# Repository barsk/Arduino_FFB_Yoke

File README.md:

# SimInvent FFB Yoke 
A Force Feedback Yoke based on 775 DC motors and an Arduino (SparkFun) Micro Pro microcontroller. 

This is a fork of [Gagagu Arduino FFB Yoke](https://github.com/gagagu/Arduino_FFB_Yoke). The goals of this fork was to lower total cost, add new features, achieve a smaller footprint, use cheaper and use more accurate AS5600 magnetic encoders and maximize pitch travel distance.

# Documentation
***All build guides and documentation for the 3D printed parts, electronics and software are in the [Wiki section!](https://github.com/barsk/Arduino_FFB_Yoke/wiki/Home)***

# Support
The [SimInvent Discord Server](https://discord.gg/cZUywYGyt6) is the main support and chat channel for this project. You are welcome to chime in and join the community there!<br>
**Bug reports**, please create an [Issue](https://github.com/barsk/Arduino_FFB_Yoke/issues) so we can track bugs and issues. 

---

> # Version 1.0 Release
> First public feature complete release with a **host of new features and performance**
>
> ## Firmware
> The firmware is now **highly optimized** compared to the previous version.
> It is now **100% compliant** with the standard Microsoft USB PID 1.0 specification with the following notable changes and bug fixes:
> * Force loop rate runs about  **2.5 times as fast** due to optimizations in every part of the firmware - 
> * Sine lookup table with interpolation replaces the computationally expensive sin() function in the force loop  - Contributing 45% of the speedup in the force loop
> * Effect direction now follows the DirectInput specification fully - Force directions was previously **inversed** in some situations
>* Multi-second FFB command lag removed when several effects were playing simultaneously with high framerate - 
> Due to inefficient USB protocol reads the input queue could build up and cause multi second lag
> * Effects no longer cancel or distort each other under load - The force calculator routine summed up effect forces 
> incorrectly causing an internal integer overflow
> * Coasting at idle - The motor output stage was driven even when idle, so the yoke was efffectively braked when zero force was applied. This has now been fixed, at 0 force, the output stage disbles leaving the yoke unpowered.
> * Handling non-linear motor response - The 775 motor driven straight from a PWM from 0-255 will yield a non-linear response. First at PWM=~25-40 the axis will start to move at all. Not handled this will create a huge deadband. We have previously handled this in the Setting tool with a "Motor Start Power" to define a starting point from which the effects should start, that settles the starting point, but the response *over* that setting will be non-linear with an initial bump unrealistically amplifying small effect forces. There are now settings in the firmware to configure the handling of this. See [Handling non-linear motor response](https://github.com/barsk/Arduino_FFB_Yoke/wiki/Firmware#handling-non-linear-motor-response) in the Wiki Firmware section.
>
> ## New pitch axis design
> 
> The pitch axis previously featured a planetary gear on the motor. That gave the axis plenty of torque, but also introduced backlash 
> and friction. The backlash creates a lot of rattle on vibration effects and the friction makes the axis a bit numb on smaller forces.
> The new design removes the planetary gear and instead uses a 14T pulley with a 720 mm belt. This trades some of torque, but the pitch axis is still about 70% stronger than roll anyway. 
> The upside is that **pitch now feels nimble and direct**, you are more connected to the sim and aircraft and can feel it in you hands.  
> 
> If you built the former 30T + gears based version you need to get a new metal motor bracket (same as on roll), a 14t pulley and a 720 mm belt. You will also need to print a new idler pulley (also 14T), print a new frame belt clamp piece for the new raised belt position, and a new pitch motor mount for the new height.
>
> The previous design with planetary gears can still be used, see Wiki for details.
> ## FFBTestTool

>There is now a new bundled **FFBTestTool.exe**, replacing the old ForceTest.exe that show you exactly what the 
> firmware sees from your built yoke, helping diagnosing magnetic encoders, travel, reversed motor wiring and 
> other faults, and confirming that every FFB effect is running and performing as expected with a graphical 
> view of the yoke and the forces applied to it.\
> Full details in https://github.com/barsk/FFBTestTool
> 
> ## Electronics
> The new PCBs (circuit boards) are now **fully tested!** Many thanks to **@PeteDDD** for his valuable contribution. All details are in the Wiki, Parts List and in the Electronics folder.

# Design and features compared to Gagagu Yoke

* Completely new CAD design with focus on easy printing and assembly.
* New PCB design.
* Magnetic AS5600 encoders featuring 12 bit accuracy, saving cost, space and weight.
* Removed planetary gears in both roll and pitch axis which introduces backlash (slop), friction and considerable weight increasing mass and inertia. Roll axis with a 56T pulley, 12T motor drive. That gives a 4.7 gear ratio which is quite enough for roll forces and provides a more nimble, lively feel than the old design. Pitch axis now uses a 14T pulley. 
* Reduced footprint (400 x 275 x 100 mm).
* Pitch travel up to 165 mm with 720 mm belt on pitch (Y) axis. 
* Configurable pitch travel range in the settings tool.
* Default centering Spring force when non-FFB games are played.
* Yoke controller is remixed so that only 3 mm brass thread inserts is used. The mount bracket is updated for strength.
* Calibration method is completely revamped. It runs automatically on first start to find the endstops (IR sensors) at the extremes of the axis travel. It can also be manually started by a button at any time. 
* The calibration data is stored in EEPROM and recalled on subsequent reboot. 
* Cable chain link. To prevent breakage of the cabling a chain link is used in the design. This will give all cables from the yoke handle and frame sensors a controlled bend characteristic with a big radius preventing acute bending and breakage. 
* A 3D printed casing with plenty of cooling slots for ventilation is part of the design and fully integrated. The casing is split up into four parts plus the front and back panels which is split in two each, providing a fully printable design despite its large size. The parts are assembled with (printed) dowels and glued or screwed together.

### Electronics and PCB (circuit boards)
**@PeteDDD** has graciously contributed new custom PCB designs. 
Gagagu version PCBs can still be used, with some modifications (see Wiki).

### Settings tool
A settings tool written in Python and Qt6. The tool features a sleek experience and features a robust and fast serial protocol.

### 3D printed parts
No 3D printed parts are the same from the Gagagu/jwryan4 project. Every part has been redesigned from the ground up with focus on easy printing, strength, functionality and minimal footprint. The IR-based end-stop sensors are now integrated into the actual design in a way that need no careful positioning as before.

### Firmware
The firmware code is *heavily modified and enhanced* with new features and updated for the new AS5600 encoders and a TCA9548 I2C mux. 
With heavy optimizations it was possible to squeeze all the performance and features into the Atmega32u4 28 KB Flash ROM of the Arduino Pro Micro with just a few bytes to spare!

### FFB Effects
The actual FFB effects are based on the [FINO](https://github.com/jmriego/Fino) project but have undergone bug fixes and heavy optimization to increase speed, lower latency and lower FLASH size.

#### Games with native FFB
For games that themselves handles standard FFB effects such as IL2 and DCS the yoke will work when connected, as it fully handles the standard DirectInput PID protocol (currently untested, but *should* work!).

 ####  Microsoft Flight Simulator, Xplane and others without FFB effects
 Since MSFS and others don't have any FFB effects implemented we have to rely on external software to interpret telemetry data from the sim and create effects accordingly. 

 * [**DirectLink** with **TelemFFB** from VPForce](https://directlink.flyfrisby.com/) A new contender, **free** download, which creates the link between TelemFFB, which formerly only could only interact with its own Rhino devices, can now interact with standard DirectInput FFB devices. Currently in Beta, but works fine with SimInvent FFB Yoke! 
 
* [FFB-Bridge](https://ffb-bridge.com/) - A great **free** force-feedback application for flight simulators on Windows, Linux, and macOS, developed and published by Rohsam Inc.

 * [XPForce](https://www.fsmissioneditor.com/product/xpforce/) - Commercial product (subscription), works for MSFS, Xplane, Flight Sim world and Prepar3D. 
 
I am not affiliated with these softwares, nor is this in any way a comprehensive list, there may be other options.

### Assembly
For easy assembly there is a number of options: 

* A printable "bracket" that can be used to position the right rail correctly. The other parts will then be easy to postition relatively that rail or the edge of the board. 
* Drill template (drawing) for the bottom board that can be printed in 1:1 scale and layed out on the board to easily position the components. 
* The STEP file of the board with all (threaded) screw holes in the correct spots can be used to machine the board on a CNC router. 

These method are described in the [Wiki Build-Guide](https://github.com/barsk/Arduino_FFB_Yoke/wiki/Build-Guide).

## Limitations
The design has some drawbacks that need to be taken in consideration.

* DC motors are not as efficent as brushless BLDC motors. They overheat sooner if pushed hard.  
* There is a slight cogging sensation in the rotation of these motors than with BLDC motors (that can use anti-cogging algorithms in the motor drivers to counter the effect)
* The microprocessor is limited to 16 MHz which leaves little headroom if many effects are playing simultaneously. There heas been a great effort put into finding optimizations on every possible front to squeeze the absolute most of this device. With about 10-15 effects playing at the same time we can do periodics (sine, triangle etc) up to about 90-100 Hz, which should cover most if not all real world scenarios. And if we reach the ceiling the periodic will drop a little in frequency, that is basically all.

The motors (775 DC) and BTS7960 43A drivers are easy to find and come at a very low cost. Better microprocessors, BLDC motors and drivers are at the next level cost wise, and what we achieve with these components is pretty impressive!
Just keep in mind the possible overheating problems and do not use strong forces sustained for a prolonged time as this can overheat the motors. Heatsinks on the motors and a fan controller that kicks in at about 40 centigrades is mandatory. When you hear the fan power up, you know you are pushing it. That said, when flying normally with the aircraft properly trimmed this practically never occurs. Heatsinks, fan controllers and fans are all in the Parts List (see [Wiki section](https://github.com/barsk/Arduino_FFB_Yoke/wiki/Part-List)).

## Credits
*I wish to thank **@PeteDDD** for invaluable help with professional level proof reading and for the new quality PCBs.*

### Some of the Github projects this is based on.
* [FINO](https://github.com/jmriego/Fino)
* [Rob Tillaart, AS5600](https://github.com/RobTillaart/Arduino/tree/master/libraries/AS5600)
* [Rob Tillaart, TCA9548](https://github.com/RobTillaart/Arduino/tree/master/libraries/TCA9548)

### Thingiverse
* [Cadet Yoke v2.0](https://www.thingiverse.com/thing:4884092)
* [Ender 3 Cable Chain](https://www.thingiverse.com/thing:2920060)

## Using this project commercially is strictly disallowed
If you want to use this project commercially please contact me.

# Disclaimer!
> [!Important]
> Use at your own risk. I am not responsible for any damage or injury to man or machine. Be careful when handling electric installations, electronics and mechanics. If handling electrical installation (230V) by yourself is not legal in your country or you feel unsure of your competence, take proffessional help! <br>
The motors are quite strong and can cause serious injuries if not handled with great caution. The yoke handle can move very quickly when power is applied. Be aware of moving parts, belts and pulleys.

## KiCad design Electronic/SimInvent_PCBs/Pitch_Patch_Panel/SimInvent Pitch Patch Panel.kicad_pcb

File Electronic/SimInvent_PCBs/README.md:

This folder contain the KiCad project files and Gerber files needed for manufacturing of the SimInvent PCBs.

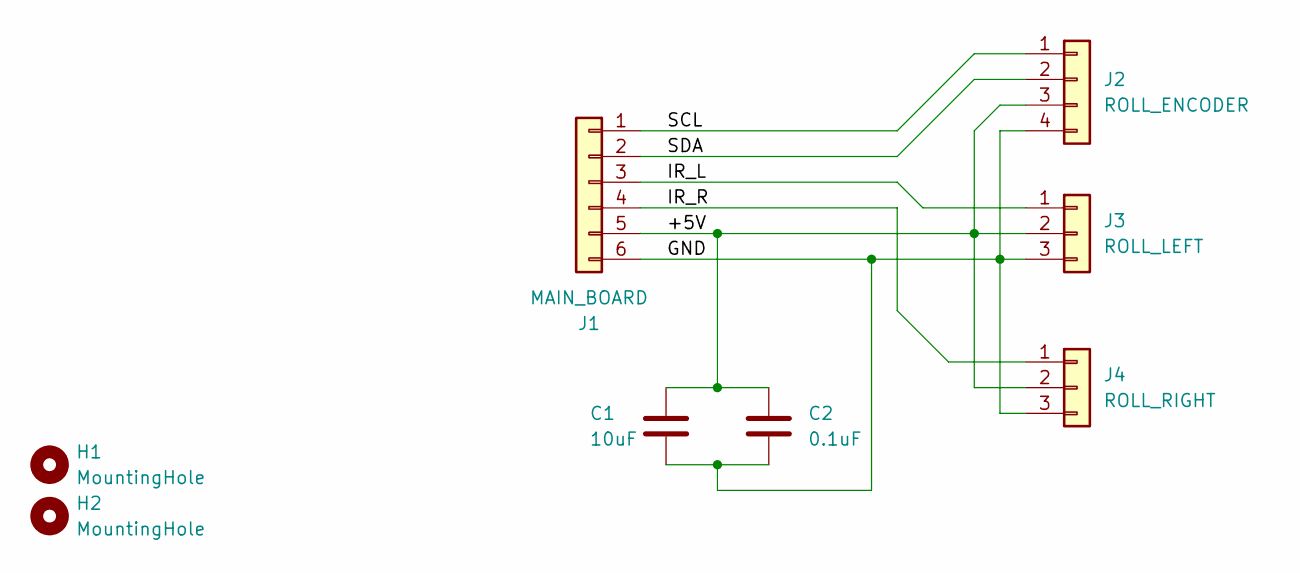
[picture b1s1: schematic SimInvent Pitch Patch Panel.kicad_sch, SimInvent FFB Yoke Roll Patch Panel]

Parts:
C1: 10uF; DUAL_CAP_2.5mm_0603
C2: 0.1uF; DUAL_CAP_2.5mm_0603
H1, H2: MountingHole; MountingHole_3.2mm_M3_DIN965
J1: MAIN_BOARD; JST_XH_B6B-XH-A_1x06_P2.50mm_Vertical
J2: ROLL_ENCODER; JST_XH_B4B-XH-A_1x04_P2.50mm_Vertical
J3: ROLL_LEFT; JST_XH_B3B-XH-A_1x03_P2.50mm_Vertical
J4: ROLL_RIGHT; JST_XH_B3B-XH-A_1x03_P2.50mm_Vertical

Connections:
/+5V: C1.1, C2.1, J1.5, J2.3, J3.2, J4.2
/GND: C1.2, C2.2, J1.6, J2.4, J3.3, J4.3
/IR_L: J1.3, J3.1
/IR_R: J1.4, J4.1
/SCL: J1.1, J2.1
/SDA: J1.2, J2.2

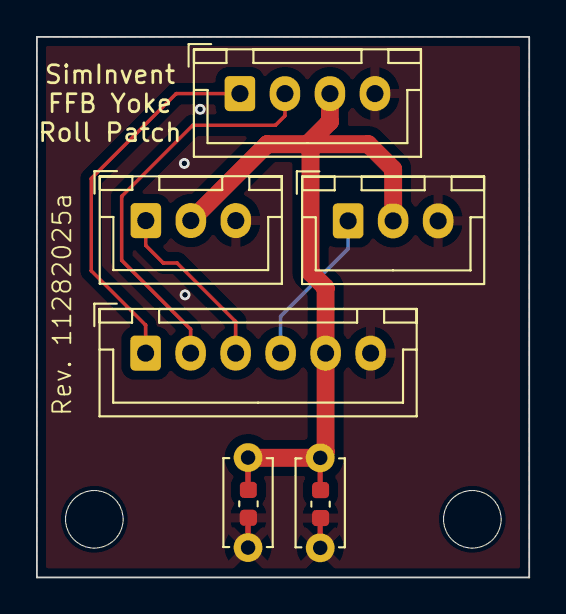
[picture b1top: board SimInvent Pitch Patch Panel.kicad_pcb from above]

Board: 2 copper layers, 27.4 x 30.0 mm, 8 parts (0 on the bottom side), 6 nets.

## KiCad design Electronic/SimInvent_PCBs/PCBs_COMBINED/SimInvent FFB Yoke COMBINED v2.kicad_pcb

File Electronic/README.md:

Contents of this folder:
* Fritzing - source files for the wiring schematics
* SimInvent_PCBs - The new PCBs by @PeteDD
* Legacy - The older Gagagu v2.0 PCBs. These are compatible, but please see the Wiki for details covering the special fixes made.
* PCB_pictures - Rendered PCB images. Note, additional images can also be viewed in the [Wiki Electronics section](https://github.com/barsk/Arduino_FFB_Yoke/wiki/Electronics)
* Wiring_diagram -  Diagram of the overall wiring

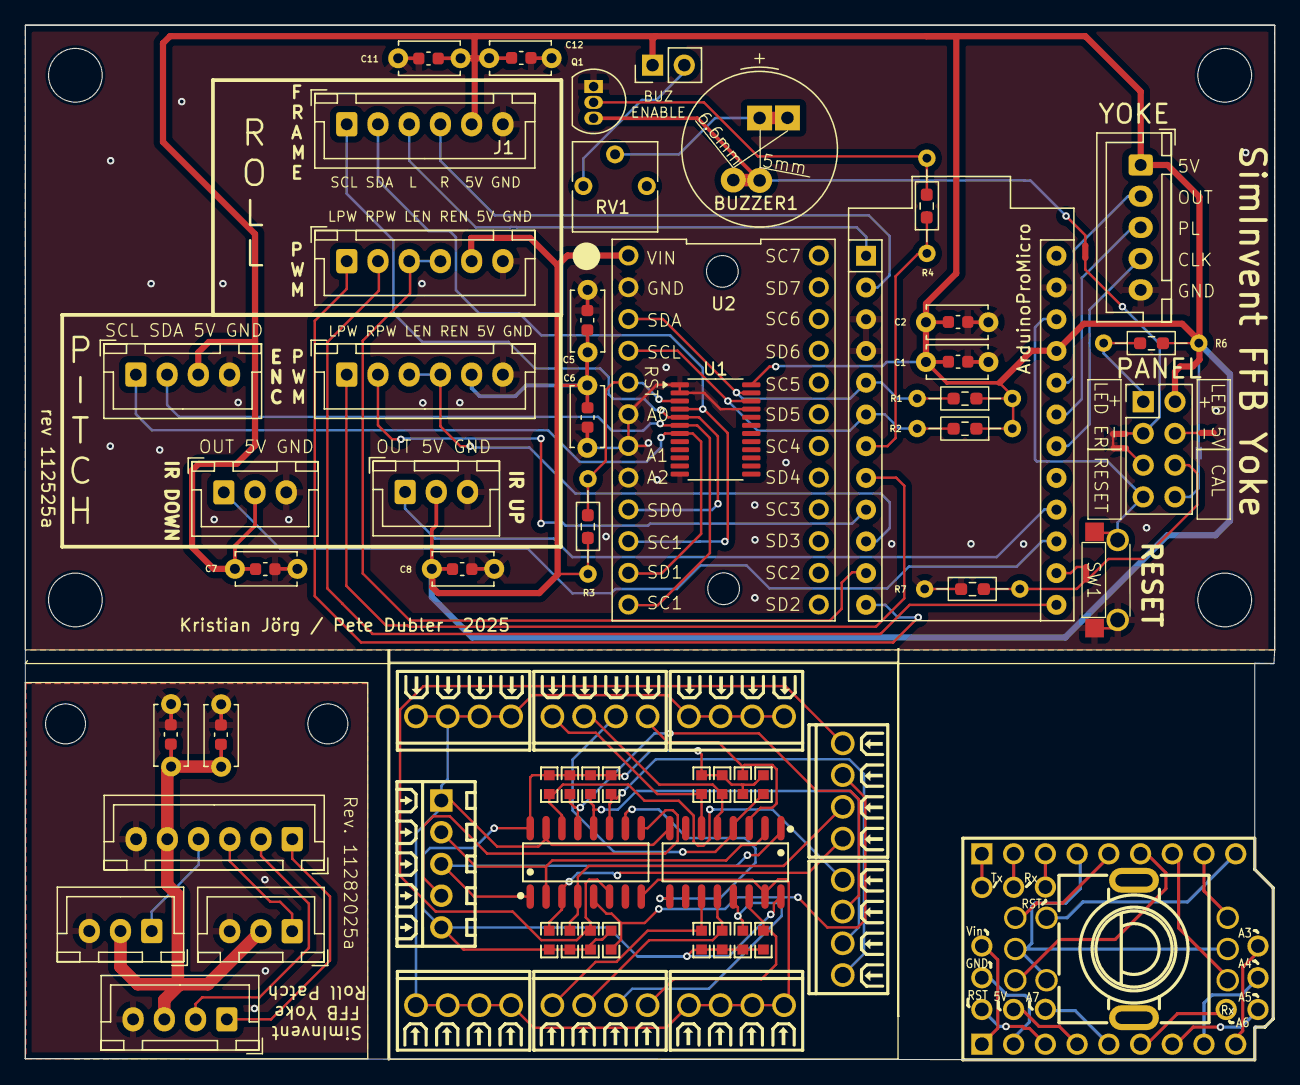
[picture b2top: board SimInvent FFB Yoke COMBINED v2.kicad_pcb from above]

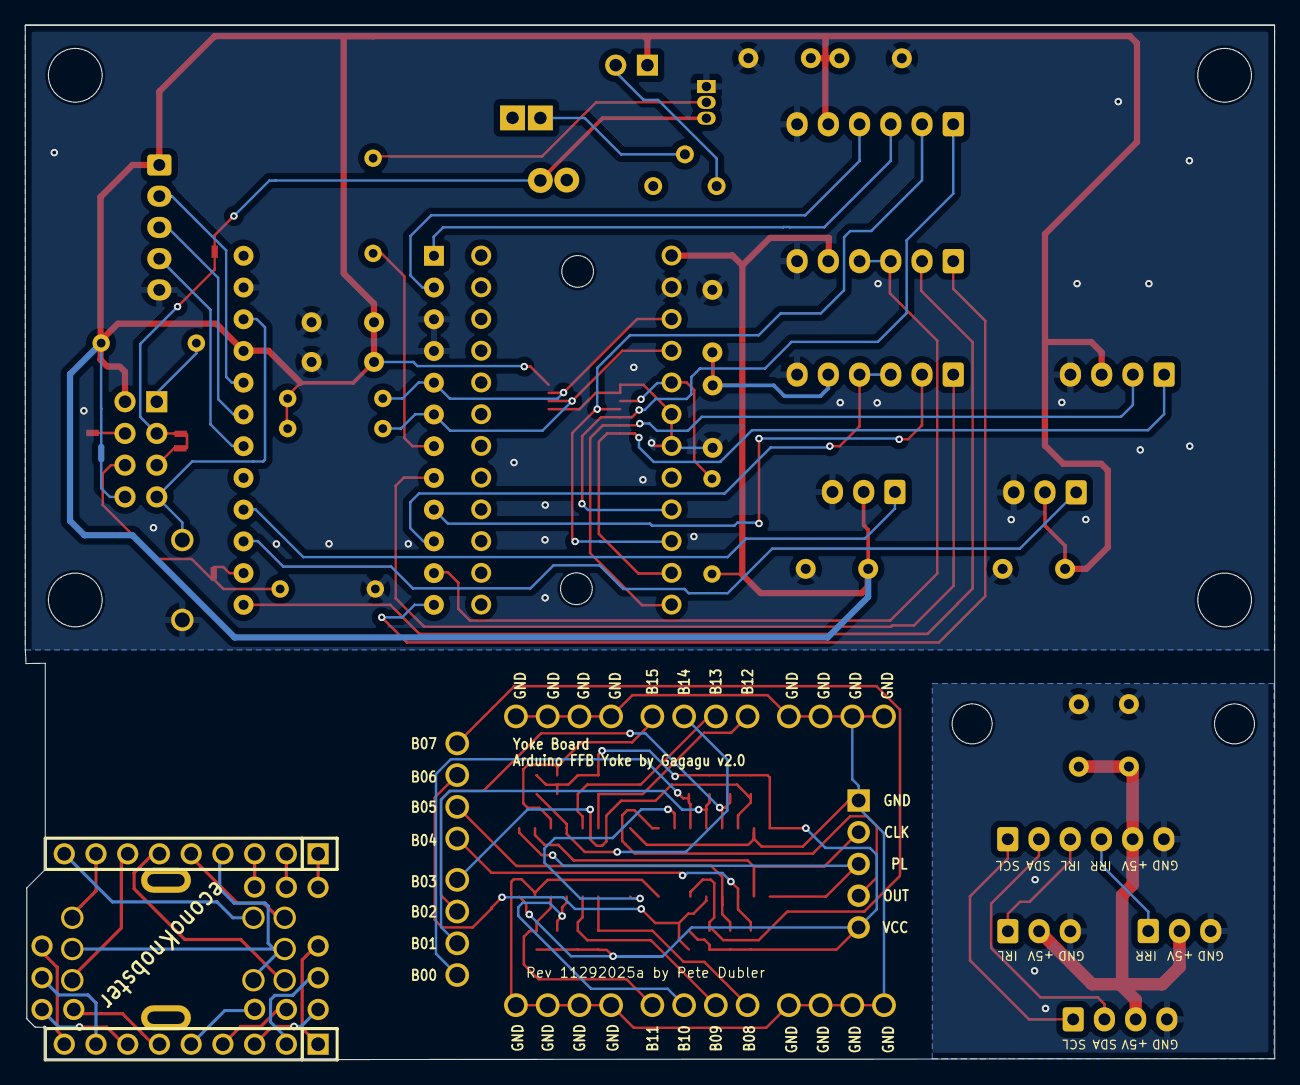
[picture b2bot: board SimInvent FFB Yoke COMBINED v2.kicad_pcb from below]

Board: 2 copper layers, 100.0 x 82.8 mm, 91 parts (2 on the bottom side), 80 nets.

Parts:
ARDUINO_PRO_MICRO1: ArduinoProMicro; Sparkfun_Pro_Micro
BUZZER1: 2700Hz; Buzzer_TDK_PS1240P02BT_D12.2mm_H6.5mm
C1, C2#2, C6, C12: 10uF; DUAL_CAP_2.5mm_0603
C1#2, C2, C5, C7, C8, C11: 0.1uF; DUAL_CAP_2.5mm_0603
H1, H2#2: MountingHole; MountingHole_3.2mm_M3_DIN965
H1#2, H2, H3, H4: MountingHole; MountingHole_4.3mm_M4_DIN965
H1#3, H2#3: HDR-TH_9P-P2.54-V-F-1
H3#2, H4#2, H5, H6, H7, H8, H9, H10, H11, H12, H13, H14: HDR-TH_1P-P2.54-V-M
IC1, IC2: SOIC-16_L9.9-W3.9-P1.27-LS6.0-BL
J1: Frame Cable; JST_XH_B6B-XH-A_1x06_P2.50mm_Vertical
J1#2: MAIN_BOARD; JST_XH_B6B-XH-A_1x06_P2.50mm_Vertical
J2: Roll Motor; JST_XH_B6B-XH-A_1x06_P2.50mm_Vertical
J2#2: ROLL_ENCODER; JST_XH_B4B-XH-A_1x04_P2.50mm_Vertical
J3: Pitch Motor; JST_XH_B6B-XH-A_1x06_P2.50mm_Vertical
J3#2: ROLL_LEFT; JST_XH_B3B-XH-A_1x03_P2.50mm_Vertical
J4: Pitch Encoder; JST_XH_B4B-XH-A_1x04_P2.50mm_Vertical
J4#2: ROLL_RIGHT; JST_XH_B3B-XH-A_1x03_P2.50mm_Vertical
J5: IR Pitch Down; JST_XH_B3B-XH-A_1x03_P2.50mm_Vertical
J6: IR Pitch Up; JST_XH_B3B-XH-A_1x03_P2.50mm_Vertical
J7: Jumper - Buzzer Active; PinHeader_1x02_P2.54mm_Vertical
J8: Yoke; JST_XH_B5B-XH-A_1x05_P2.50mm_Vertical
J9: Conn_02x04_Counter_Clockwise; PinHeader_2x04_P2.54mm_Vertical
NT1, NT2, NT3, NT4, NT5, NT6, NT7: NetTie_2; NetTie-2_SMD_Pad0.5mm
Q1: 2N4401; TO-92L_Inline
R1, R2, R3, R7: 10K0; DUAL_RESISTOR_7.62mm_0605
R1#2, R2#2, R3#2, R4#2, R5, R6, R7#2, R8, R9, R10, R11, R12, R13, R14, R15, R16: R0603
R4: 2K0; DUAL_RESISTOR_7.62mm_0605
R6#2: 220; DUAL_RESISTOR_7.62mm_0605
RV1: R_Potentiometer; Potentiometer_Vishay_T73YP_Vertical
SW1: PTS636SM43LFS 6X3.5MM; DUAL_TACTILE_SWITCH
SW1#2: SW-TH_EC11EBB24C03
U1: CONN-TH_5P-P2.54_MX128-2.54-05P-GN01-CU-Y-A
U1#2: TCA9548APWR; TSSOP-24_4.4x7.8mm_P0.65mm
U2, U3, U4, U5, U6, U7, U8, U9: CONN-TH_4P-P2.54_MX128-2.54-GN01-04P-CU-Y-A
U2#2: TCA9548A Module

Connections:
5V_POWER_LED+: J9.2, NT5.1
5V_POWER_LED-: J9.4, NT1.2
$1N177: H1#3.4, SW1#2.2, SW1#2.5, SW1#2.8
$1N178: H1#3.5, SW1#2.3
$1N179: H1#3.6, SW1#2.1
$1N180: H1#3.7, SW1#2.6
$1N181: H1#3.8, SW1#2.4
$1N182: H1#3.9, SW1#2.9
$1N1235: H1#3.1, H14.1
$1N1240: H1#3.3, H12.1
$1N1261: H1#3.2, H13.1
$1N1270: H2#3.1, H3#2.1
$1N1276: H2#3.2, H4#2.1
$1N1286: H2#3.3, H5.1
$1N1295: H2#3.4, H6.1
$1N1304: H2#3.5, H7.1
$1N1314: H2#3.6, H8.1
$1N1321: H2#3.7, H9.1
$1N1328: H2#3.8, H10.1
$1N1335: H2#3.9, H11.1
+5V: ARDUINO_PRO_MICRO1.21 (5V), C1#2.1, C2#2.1, C5.1, C6.1, C7.2, C8.2, C11.1, C12.1, J1.5, J2.5, J3.5, J4.3, J5.2, J6.2, J7.1, J8.1, NT4.2, NT5.2, R1.1, R2.1, R3.1, R6#2.1, U1#2.24 (VCC), U2#2.1 (VCC)
/+5V: C1.1, C2.1, J1#2.5, J2#2.3, J3#2.2, J4#2.2
/Buzzer-: BUZZER1.2, NT7.2, Q1.3 (C)
/GND: C1.2, C2.2, J1#2.6, J2#2.4, J3#2.3, J4#2.3
/IR_L: J1#2.3, J3#2.1
/IR_R: J1#2.4, J4#2.1
/SCL: J1#2.1, J2#2.1
/SDA: J1#2.2, J2#2.2
BUZZER: ARDUINO_PRO_MICRO1.7 (D4/A6), R4.1
CALIBRATION_BUTTON+: J9.8, NT4.1
CALIBRATION_BUTTON-: J9.6, NT6.1, R7.1
ERROR_LED+: J9.1, R6#2.2
ERROR_LED-: J9.3, NT2.2, NT7.1
E_PWM_PITCH: ARDUINO_PRO_MICRO1.10 (D7), J3.3, J3.4
E_PWM_ROLL: ARDUINO_PRO_MICRO1.11 (D8/A8), J2.3, J2.4
GND: ARDUINO_PRO_MICRO1.3 (GND), ARDUINO_PRO_MICRO1.4 (GND), ARDUINO_PRO_MICRO1.23 (GND), C1#2.2, C2#2.2, C5.2, C6.2, C7.1, C8.1, C11.2, C12.2, J1.6, J2.6, J3.6, J4.4, J5.3, J6.3, J8.5, NT1.1, NT2.1, NT3.1, Q1.1 (E), R7.2, SW1.1, U1#2.1 (A0), U1#2.2 (A1), U1#2.12 (GND), U1#2.21 (A2), U2#2.2 (GND), U2#2.6 (A0), U2#2.7 (A1), U2#2.8 (A2)
I2C_MUX_SCL_INPUT: ARDUINO_PRO_MICRO1.6 (D3/INT0/SCL), R2.2, U1#2.22 (SCL), U2#2.4 (SCL)
I2C_MUX_SDA_INPUT: ARDUINO_PRO_MICRO1.5 (D2/INT1/SDA), R1.2, U1#2.23 (SDA), U2#2.3 (SDA)
IC1_10: IC1.10, IC2.9
INT_CALIBRATION: ARDUINO_PRO_MICRO1.14 (D16/MOSI), NT6.2
INT_IR_P_DOWN: ARDUINO_PRO_MICRO1.15 (D14/MISO), J5.1
INT_IR_P_UP: ARDUINO_PRO_MICRO1.16 (SCK/D15), J6.1
INT_IR_R_LEFT: ARDUINO_PRO_MICRO1.1 (TX), J1.3
INT_IR_R_RIGHT: ARDUINO_PRO_MICRO1.2 (RX), J1.4
LPWM_PITCH: ARDUINO_PRO_MICRO1.8 (D5), J3.1
LPWM_ROLL: ARDUINO_PRO_MICRO1.12 (D9/A9), J2.1
unnamed: BUZZER1.1, RV1.2
unnamed: J7.2, RV1.3
unnamed: Q1.2 (B), R4.2
unnamed: R3.2, U1#2.3 (~RESET), U2#2.5 (~RESET)
PITCH_ENC_SCL: J4.1, U1#2.7 (SC1), U2#2.11 (SC1)
PITCH_ENC_SDA: J4.2, U1#2.6 (SD1), U2#2.12 (SD1)
RESET_BUTTON: ARDUINO_PRO_MICRO1.22 (RST), J9.7, SW1.2
RESET_GND: J9.5, NT3.2
ROLL_ENC_SCL: J1.1, U1#2.5 (SC0), U2#2.9 (SC0)
ROLL_ENC_SDA: J1.2, U1#2.4 (SD0), U2#2.10 (SD0)
RPWM_PITCH: ARDUINO_PRO_MICRO1.9 (D6/A7), J3.2
RPWM_ROLL: ARDUINO_PRO_MICRO1.13 (D10/A10), J2.2
YOKE0: IC1.11, R1#2.2, U6.1
YOKE1: IC1.12, R2#2.2, U6.2
YOKE2: IC1.13, R3#2.2, U6.3
YOKE3: IC1.14, R4#2.2, U6.4
YOKE4: IC1.3, R5.2, U8.1
YOKE5: IC1.4, R6.2, U8.2
YOKE6: IC1.5, R7#2.2, U8.3
YOKE7: IC1.6, R8.2, U8.4
YOKE8: IC2.11, R16.2, U2.1
YOKE9: IC2.12, R15.2, U2.2
YOKE10: IC2.13, R14.2, U2.3
YOKE11: IC2.14, R13.2, U2.4
YOKE12: IC2.3, R12.2, U4.1
YOKE13: IC2.4, R11.2, U4.2
YOKE14: IC2.5, R10.2, U4.3
YOKE15: IC2.6, R9.2, U4.4
YOKE_CLK: ARDUINO_PRO_MICRO1.18 (A1/D19), IC1.2, IC2.2, J8.4, U1.2
YOKE_GND: IC1.8, IC1.15, IC2.8, IC2.15, U1.1, U3.1, U3.2, U3.3, U3.4, U5.1, U5.2, U5.3, U5.4, U7.1, U7.2, U7.3, U7.4, U9.1, U9.2, U9.3, U9.4
YOKE_OUT: ARDUINO_PRO_MICRO1.20 (A3/D21), J8.2
YOKE_OUTPUT: IC1.9, U1.4
YOKE_PL: ARDUINO_PRO_MICRO1.19 (A2/D20), IC1.1, IC2.1, J8.3, U1.3
YOKE_VCC: IC1.16, IC2.16, R1#2.1, R2#2.1, R3#2.1, R4#2.1, R5.1, R6.1, R7#2.1, R8.1, R9.1, R10.1, R11.1, R12.1, R13.1, R14.1, R15.1, R16.1, U1.5

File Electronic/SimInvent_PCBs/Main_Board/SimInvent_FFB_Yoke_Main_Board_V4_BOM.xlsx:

Designator | Comment | 'Footprint' | LCSC | 'Qty'
BUZZER1 | 2700Hz passive Fuet FS9012-03 | Buzzer_Beeper:Buzzer6mm | C96256 | 1
C1,C5,C7,C8,C11 | 0.1uF | MyFootprints:DUAL_CAP_2.5mm_0603 | C14663 | 5
C2,C6,C12 | 10uF | MyFootprints:DUAL_CAP_2.5mm_0603 | C19702 | 3
J1 | Frame Cable | Connector_JST:JST_XH_B6B-XH-A_1x06_P2.50mm_Vertical | C144397 | 1
J2 | Roll Motor | Connector_JST:JST_XH_B6B-XH-A_1x06_P2.50mm_Vertical | C144397 | 1
J3 | Pitch Motor | Connector_JST:JST_XH_B6B-XH-A_1x06_P2.50mm_Vertical | C144397 | 1
J4 | Pitch Encoder | Connector_JST:JST_XH_B4B-XH-A_1x04_P2.50mm_Vertical | C144395 | 1
J5 | IR Pitch Down | Connector_JST:JST_XH_B3B-XH-A_1x03_P2.50mm_Vertical | C144394 | 1
J6 | IR Pitch Up | Connector_JST:JST_XH_B3B-XH-A_1x03_P2.50mm_Vertical | C144394 | 1
J7 | Jumper - Buzzer Active | Connector_PinHeader_2.54mm:PinHeader_1x02_P2.54mm_Vertical | C492401 | 1
J8 | Yoke | Connector_JST:JST_XH_B5B-XH-A_1x05_P2.50mm_Vertical | C161872 | 1
J9 | Conn_02x04_Counter_Clockwise | Connector_PinHeader_2.54mm:PinHeader_2x04_P2.54mm_Vertical | C492421 | 1
Q1 | MMT4401 alternative | Package_TO_SOT_SMD:SOT-23 | C181123 | 1
R1,R2,R3,R7 | 10K0 0603 | MyFootprints:DUAL_RESISTOR_7.62mm_0605 | C25804 | 4
R4 | 2K0 0603 | MyFootprints:DUAL_RESISTOR_7.62mm_0605 | C22975 | 1
R5,R6 | 220ohm 0603 | MyFootprints2:DUAL_RESISTOR_7.62mm_0605 | C22962 | 2
RV1 | 3296W 500ohm | SamacSys_Parts:3296W1503LF | C48641775 | 1
SW1 | PTS636SM43LFS 6X3.5MM | MyFootprints:DUAL_TACTILE_SWITCH | C2689636 | 1
U1 | TCA9548APWR | Package_SO:TSSOP-24_4.4x7.8mm_P0.65mm | C130026 | 1
D2 |  | DO NOT POPULATE |  | 1
J112,J113,J114 | 1x12P 2.54mm female pin socket THT | KH-2.54FH-1X12P-H8.5 | C2905419 | 3
J111 | 2x12P 2.54mm female pin socket THT | DS1023-2*12SF11 | C92265 | 1

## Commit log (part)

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2025-07-29 Update README.md
    Info about the goals of this fork
2025-11-02 Initial commit on the fork
2025-11-03 Spelling fixes and git control files removed
2025-11-03 Updated src folders for PlatformIO
2025-11-03 PlatformIO files
2025-11-19 Major project update.
2025-11-20 Improve clarity and grammar
    Updated README.md for clarity and grammar improvements.
2025-11-20 Create README for alternative casing design
    Added a README file for the alternative casing design.
2025-11-23 Add README to CAD folder
2025-11-24 PD added STLs for standoff mount for new PCB and Motor Driver mount "lite" version, using less plastic.
2025-11-28 SimInvent PCB Folders added to Electronics Folder
2025-12-12 Updated for new PCBs version
2025-12-12 Revise README with new features and credits
    Updated README to reflect new features, PCB designs, and credits.
2025-12-19 Updated Frame, Yoke Controller Front and PCB standoff
2025-12-19 Updated PCB Standoff STL
2025-12-20 Updated CAD files after +10 mm length changes
2025-12-20 Updated Drill templete after + 10 mm change.
2026-02-18 The pitch and roll initial settings were reversed. The setting of initial EEPROM values was buggy.
2026-02-18 Update README with firmware fix and speed limiter notes
    Added important notes about firmware bug fixes and speed limiter functionality.
2026-02-19 Update firmware version to 2, forcing new defaults in EEPROM
2026-02-21 Initial calibration run bugs fixed
2026-02-21 Revise firmware notes and speed limiter instructions
    Updated README to clarify firmware bug fixes and speed limiter functionality.
2026-04-02 Added missing Rail mount helper.stl
2026-04-09 Add files via upload
    SimInvent FFB Yoke Main Board V 4 finalized 4 April 2026
    Includes BOM file (in GERBERS directory) for JLCPCB assembly with SMD parts.
    Also, combined board gerber files (In-Yoke Board, Patch Board, Main Yoke Board, and econoKnobster boards on one PCB
2026-05-14 Cleanup and release of v4 PCBs
2026-05-14 Yoke Tool 1.0 release, hidden Speed control slider
2026-05-16 Added yoke controller wiring sketch
2026-05-16 Updated controllerwiring sketch image file
2026-05-16 Added missing resitor to the 24V LED indicator in wiring sketch
2026-06-10 Add support section to README
    Added support section with Discord link and issue reporting instructions.
2026-06-10 Update Discord server link in README
